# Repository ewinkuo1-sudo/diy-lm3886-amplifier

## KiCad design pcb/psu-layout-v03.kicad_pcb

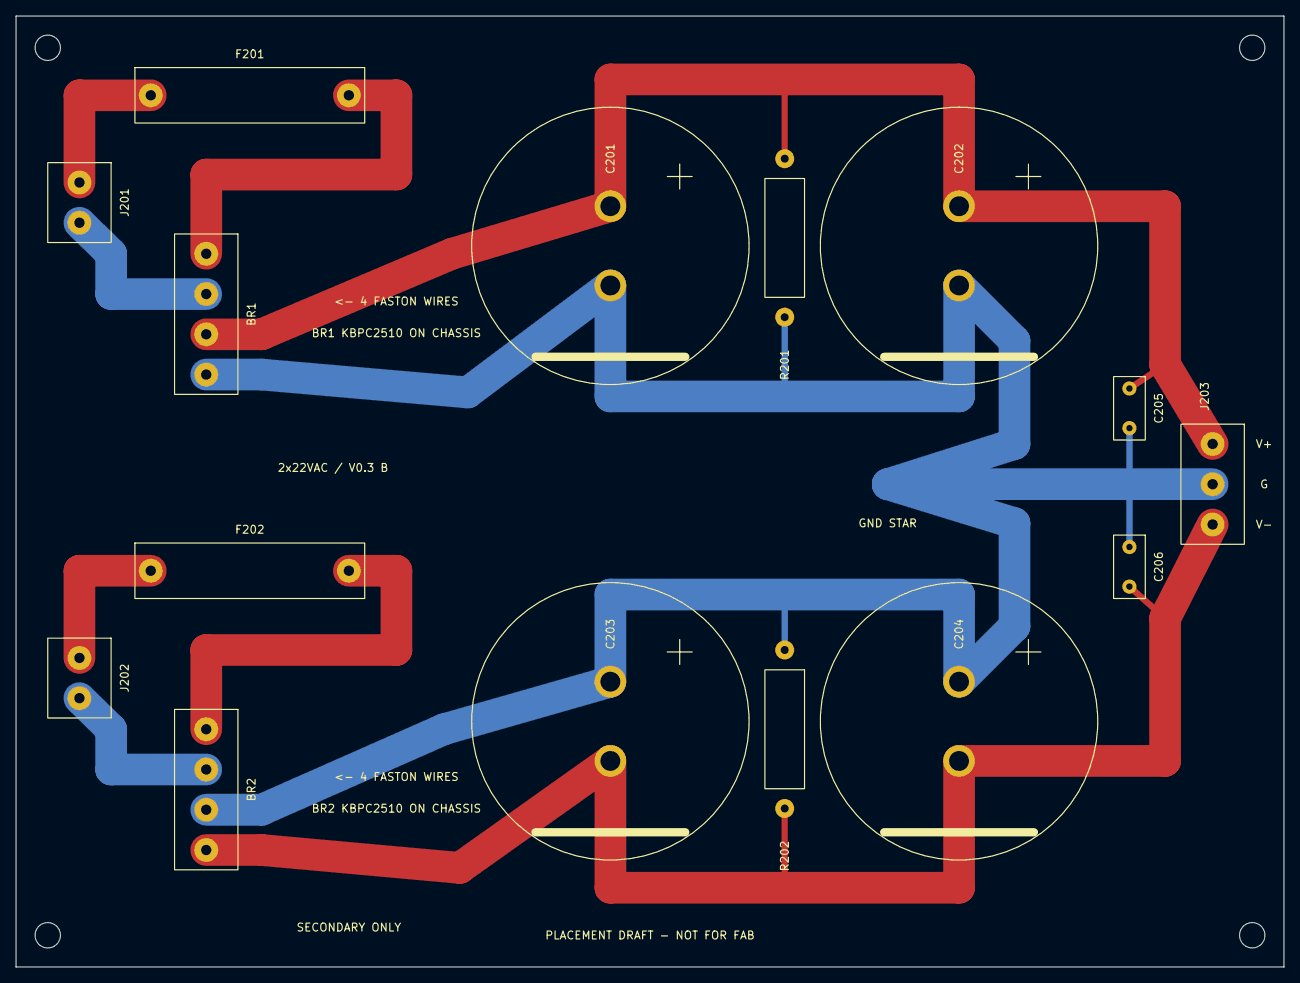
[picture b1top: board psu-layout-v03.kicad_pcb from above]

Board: 2 copper layers, 160.0 x 120.0 mm, 19 parts (0 on the bottom side), 9 nets.

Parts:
BR1, BR2: >=15A / >=200V TBD; BridgeTerminal4_P5.08
C201, C202, C203, C204: 10000u / 63V; CP_D35_P10
C205, C206: 100n / 100V film; Film_P5
F201, F202: TBD per transformer; Fuse5x20_P25
H1, H2, H3, H4: M3 provisional
J201: T1 SEC 1; Terminal2_P5.08
J202: T1 SEC 2; Terminal2_P5.08
J203: TO AMP J5; Terminal3_P5.08
R201, R202: 2.2k / 2W BLEED; R_2W_P20

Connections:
GND: BR1.N, BR2.P, C201.2, C202.2, C203.1, C204.1, C205.2, C206.1, J203.2, R201.2, R202.1
NEG_AC1: F202.1, J202.1
NEG_AC2: BR2.AC2, J202.2
NEG_AC_FUSED: BR2.AC1, F202.2
POS_AC1: F201.1, J201.1
POS_AC2: BR1.AC2, J201.2
POS_AC_FUSED: BR1.AC1, F201.2
VCC: BR1.P, C201.1, C202.1, C205.1, J203.1, R201.1
VEE: BR2.N, C203.2, C204.2, C206.2, J203.3, R202.2

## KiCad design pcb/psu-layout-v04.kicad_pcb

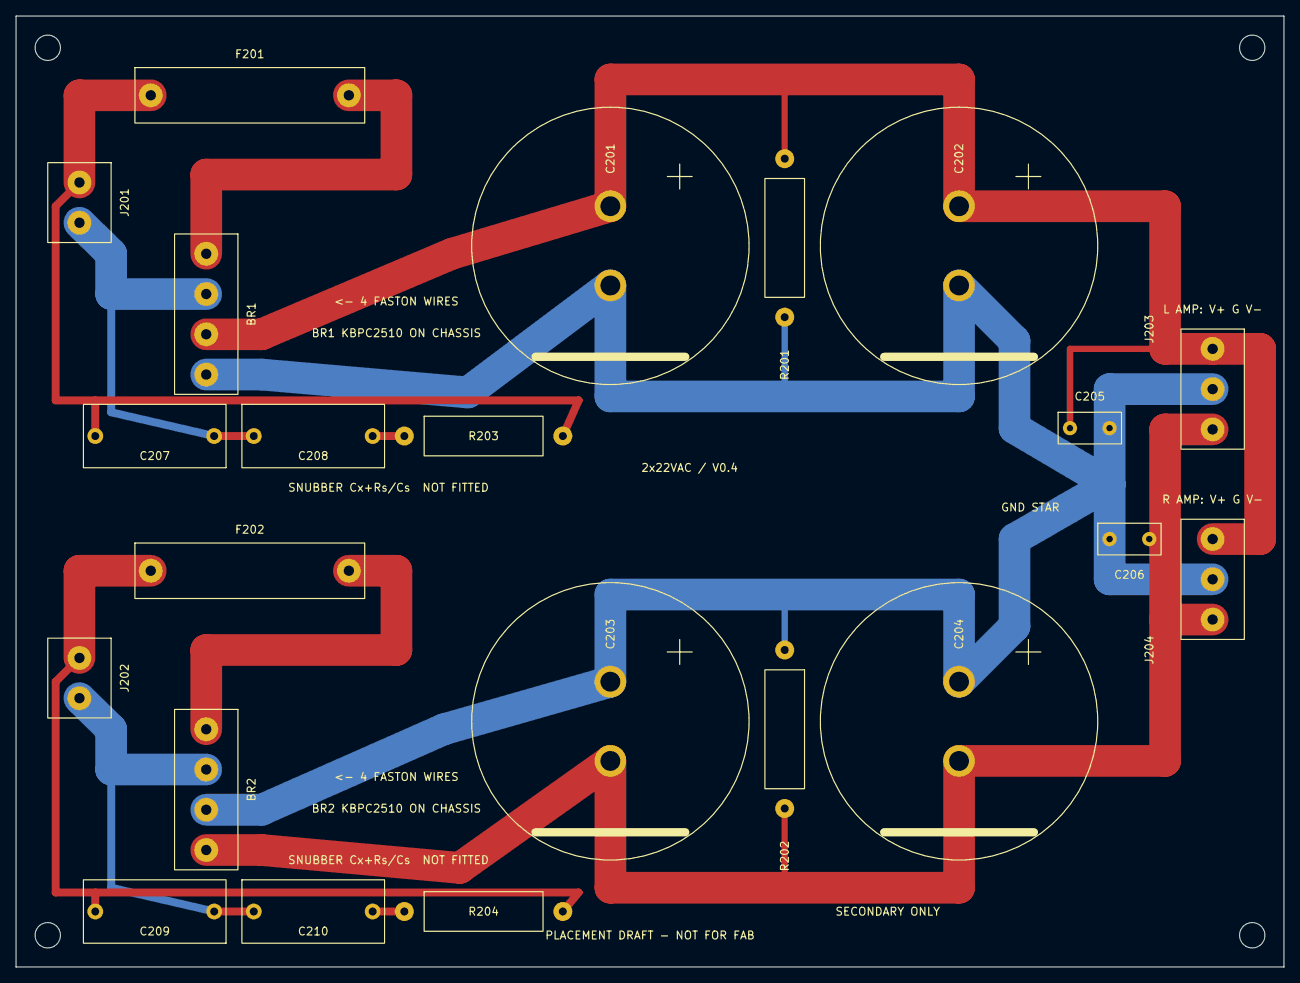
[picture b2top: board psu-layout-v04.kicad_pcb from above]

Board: 2 copper layers, 160.0 x 120.0 mm, 26 parts (0 on the bottom side), 11 nets.

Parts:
BR1, BR2: >=15A / >=200V TBD; BridgeTerminal4_P5.08
C201, C202, C203, C204: 10000u / 63V; CP_D35_P10
C205, C206: 100n / 100V film; Film_P5
C207, C209: TBD Cx (10n / 630V film); Film_P15
C208, C210: TBD Cs (150n / 630V film); Film_P15
F201, F202: TBD per transformer; Fuse5x20_P25
H1, H2, H3, H4: M3 provisional
J201: T1 SEC 1; Terminal2_P5.08
J202: T1 SEC 2; Terminal2_P5.08
J203: TO L AMP J5; Terminal3_P5.08
J204: TO R AMP J5; Terminal3_P5.08
R201, R202: 2.2k / 2W BLEED; R_2W_P20
R203, R204: TBD Rs (10R-47R / 2W); R_2W_P20

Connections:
GND: BR1.N, BR2.P, C201.2, C202.2, C203.1, C204.1, C205.2, C206.1, J203.2, J204.2, R201.2, R202.1
NEG_AC1: C209.2, F202.1, J202.1, R204.2
NEG_AC2: BR2.AC2, C209.1, C210.1, J202.2
NEG_AC_FUSED: BR2.AC1, F202.2
NEG_SNUB: C210.2, R204.1
POS_AC1: C207.2, F201.1, J201.1, R203.2
POS_AC2: BR1.AC2, C207.1, C208.1, J201.2
POS_AC_FUSED: BR1.AC1, F201.2
POS_SNUB: C208.2, R203.1
VCC: BR1.P, C201.1, C202.1, C205.1, J203.1, J204.1, R201.1
VEE: BR2.N, C203.2, C204.2, C206.2, J203.3, J204.3, R202.2
